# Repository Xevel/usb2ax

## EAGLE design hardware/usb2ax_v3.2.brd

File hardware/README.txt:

usb2ax Eagle files
==================

usb2ax_v3.2 : Second production version, cheaper (uses OPL parts instead of some costly components).

usb2ax_v3.1 : First production version. Added protection against short-circuit between +12V and DATA, and better hackability (expension pads).

usb2ax_mini : A smaller version of the v3.0 with a PCB USB connector and audacious placement of the Dynamixel connector.

usb2ax_v3.0 : MCU in QFN package, real USB connector

usb2ax_v2 (removed) : aborted version similar to v1.

usb2ax_v1 : Initial realease. MCu in TQFP package, PCB USB connector, protections lacking.

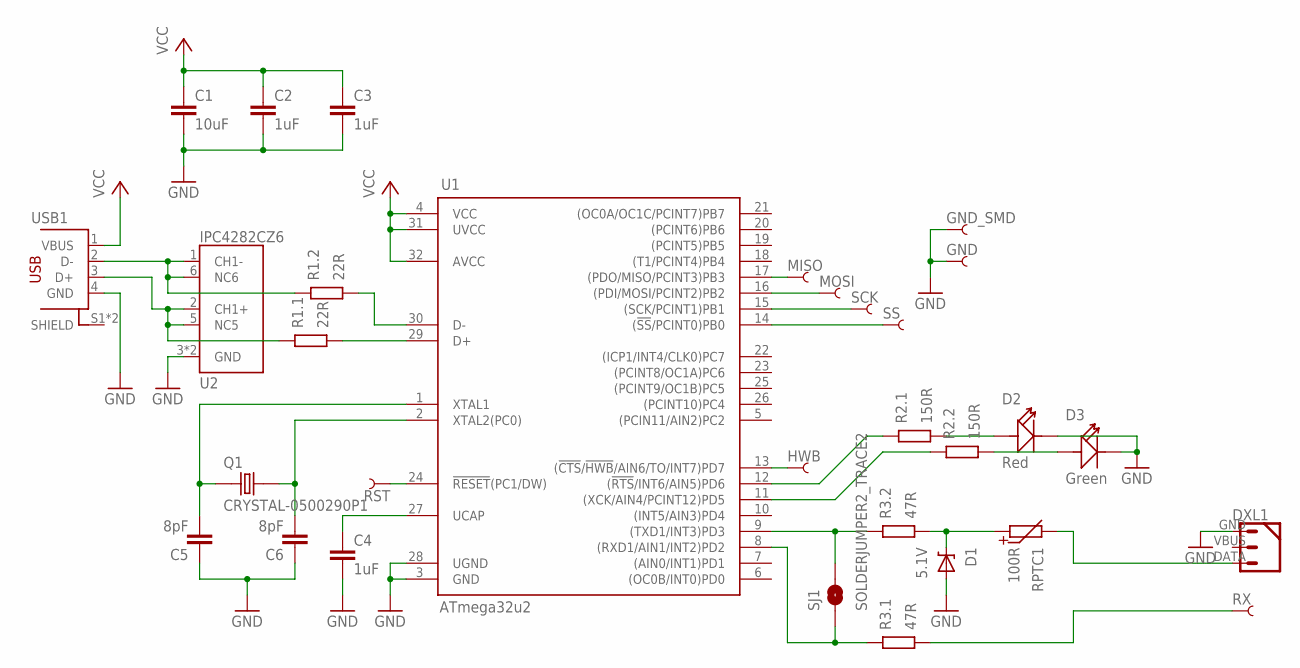
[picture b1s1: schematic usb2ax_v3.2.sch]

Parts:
C1: 10uF; 0805_L
C2, C3, C4: 1uF; 0402_N
C5, C6: 8pF; 0402_N
D1: 5.1V; SOD-923_N
D2: Red; LED0603
D3: Green; LED0603
DXL1: DYNAMIXEL_3POS; DYMANIXEL_3POS_RIGHT
GND: PIN_SMD_2X2.5
GND_SMD: PIN_SMD_2X2.5
HWB: PIN_SMD_2X2.5
MISO: PIN_SMD_2X2.5
MOSI: PIN_SMD_2X2.5
Q1: CRYSTAL-0500290P1; 2P-SMD-5.0X3.2
R1: 22R; ARRAY_0402_65P_2_N
R2: 150R; ARRAY_0402_65P_2_N
R3: 47R; ARRAY_0402_65P_2_N
RPTC1: 100R; 0603_N
RST: PIN_SMD_2X2.5
RX: PIN_THT_0.8; PIN_0.8
SCK: PIN_SMD_2X2.5
SJ1: SOLDERJUMPER2_TRACE2; SJ_2S-TRACE2
SS: PIN_SMD_2X2.5
U1: ATmega32u2; QFN-32_50P_L_MOD
U2: IPC4282CZ6; XSON6_N
USB1: USB-STANDARD-PLUG_A_THT; USB-A-THT

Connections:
GND: C1.2, C2.2, C3.2, C4.2, C5.1, C6.1, D1.A, D2.-, D3.-, DXL1.GND (1), GND.PIN, GND_SMD.PIN, U1.3 (GND), U1.28 (UGND), U2.3 (GND), U2.4 (GND), USB1.4 (GND)
HWB: HWB.PIN, U1.13 ((!CTS!/!HWB!/AIN6/TO/INT7)PD7)
unnamed: R3.4 (2), SJ1.2, U1.9 ((TXD1/INT3)PD3)
unnamed: R3.3 (2), SJ1.1, U1.8 ((RXD1/AIN1/INT2)PD2)
unnamed: C4.1, U1.27 (UCAP)
unnamed: D1.C, R3.1, RPTC1.1
unnamed: R2.4 (2), U1.11 ((XCK/AIN4/PCINT12)PD5)
unnamed: DXL1.DATA (3), RPTC1.2
unnamed: C6.2, Q1.2, U1.2 (XTAL2(PC0))
unnamed: C5.2, Q1.1, U1.1 (XTAL1)
unnamed: R1.1, U1.30 (D-)
unnamed: R1.2 (1), U1.29 (D+)
unnamed: R1.4 (2), U2.1 (CH1-), U2.6 (NC6), USB1.2 (D-)
unnamed: R1.3 (2), U2.2 (CH1+), U2.5 (NC5), USB1.3 (D+)
unnamed: D2.+, R2.2 (1)
unnamed: D3.+, R2.1
unnamed: R2.3 (2), U1.12 ((!RTS!/INT6/AIN5)PD6)
unnamed: R3.2 (1), RX.PIN
unnamed: MISO.PIN, U1.17 ((PDO/MISO/PCINT3)PB3)
unnamed: MOSI.PIN, U1.16 ((PDI/MOSI/PCINT2)PB2)
unnamed: SCK.PIN, U1.15 ((SCK/PCINT1)PB1)
unnamed: SS.PIN, U1.14 ((!SS!/PCINT0)PB0)
RST: RST.PIN, U1.24 (!RESET!(PC1/DW))
VCC: C1.1, C2.1, C3.1, U1.4 (VCC), U1.31 (UVCC), U1.32 (AVCC), USB1.1 (VBUS)

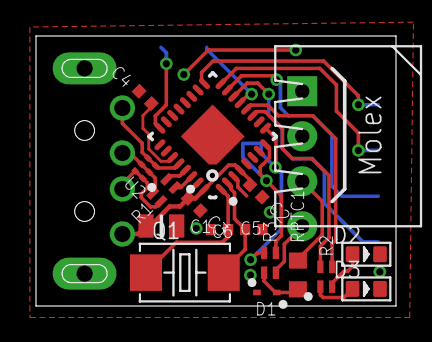
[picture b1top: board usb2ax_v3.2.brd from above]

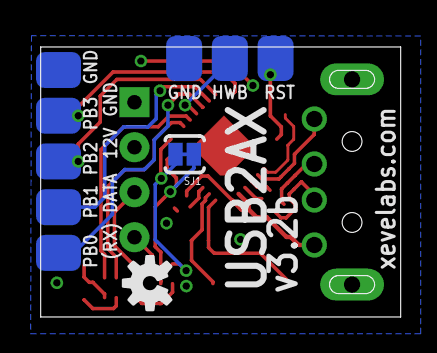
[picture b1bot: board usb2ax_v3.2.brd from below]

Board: 2 copper layers, 20.0 x 15.0 mm, 29 parts (10 on the bottom side), 24 nets.

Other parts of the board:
U$1: OSHW-LOGO-S

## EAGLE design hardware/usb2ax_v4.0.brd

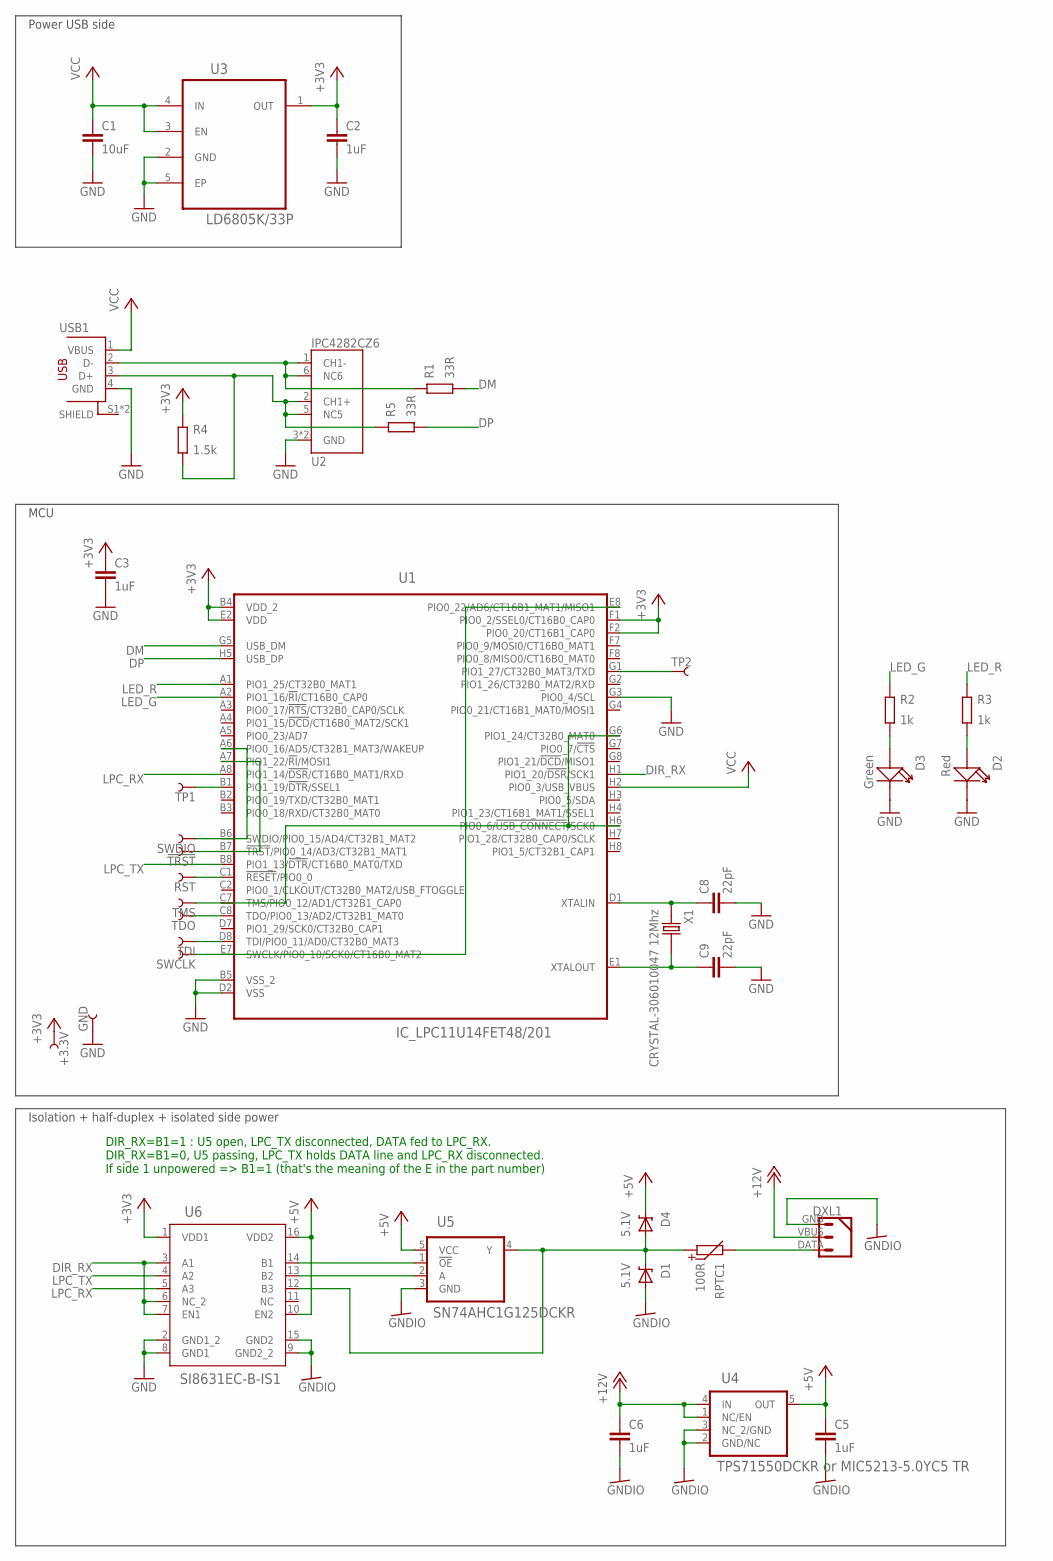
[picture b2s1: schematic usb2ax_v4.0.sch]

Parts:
!TRST: PIN_SMD_1X1
+3.3V: PIN_SMD_1X1
C1: 10uF; 0805_L
C2, C3, C5, C6: 1uF; 0402_N
C8, C9: 22pF; 0402_N
D1, D4: 5.1V; SOD-923_N
D2: Red; LED0603
D3: Green; LED0603
DXL1: DYNAMIXEL_3POS-R; DYNAMIXEL_3POS_RIGHT
GND: PIN_SMD_1X1
R1, R5: 33R; 0201_N
R2, R3: 1k; 0201_N
R4: 1.5k; 0201_N
RPTC1: 100R; 0603_N
RST: PIN_SMD_1X1
SWCLK: PIN_SMD_1X1
SWDIO: PIN_SMD_1X1
TDI: PIN_SMD_1X1
TDO: PIN_SMD_1X1
TMS: PIN_SMD_1X1
TP1, TP2: PIN_SMD_1X1
U1: IC_LPC11U14FET48/201; BGA48C50P8X8_460X460X110
U2: IPC4282CZ6; XSON6_N
U3: LD6805K/33P; NXP_LD6805
U4: TPS71550DCKR or MIC5213-5.0YC5 TR; SOT65P210X110-5N
U5: SN74AHC1G125DCKR; SOT65P210X110-5N
U6: SI8631EC-B-IS1; SOIC-16
USB1: USB-STANDARD-PLUG_A_THT; USB-A-THT
X1: CRYSTAL-306010047 12Mhz; 2P-SMD-5.0X3.2

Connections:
!TRST: !TRST.P$1, U1.A7 (PIO1_22/!RI!/MOSI1), U1.B7 (!TRST!/PIO0_14/AD3/CT32B1_MAT1)
+3V3: +3.3V.P$1, C2.1, C3.1, R4.2, U1.B4 (VDD_2), U1.E2 (VDD), U1.F1 (PIO0_2/SSEL0/CT16B0_CAP0), U1.F2 (PIO0_20/CT16B1_CAP0), U3.1 (OUT), U6.1 (VDD1)
+5V: C5.1, D4.C, U4.5 (OUT), U5.5 (VCC), U6.10 (EN2), U6.16 (VDD2)
+12V: C6.1, DXL1.VBUS (2), U4.1 (NC/EN), U4.4 (IN)
DIR_RX: U1.H1 (PIO1_20/!DSR!/SCK1), U6.3 (A1), U6.6 (NC_2), U6.7 (EN1)
DM: R1.1, U1.G5 (USB_DM)
DP: R5.1, U1.H5 (USB_DP)
GND: C1.2, C2.2, C3.2, C8.2, C9.2, D2.-, D3.-, GND.P$1, U1.B5 (VSS_2), U1.D2 (VSS), U1.G3 (PIO0_4/SCL), U2.3 (GND), U2.4 (GND), U3.2 (GND), U3.5 (EP), U6.2 (GND1_2), U6.8 (GND1), USB1.4 (GND)
GNDIO: C5.2, C6.2, D1.A, DXL1.GND (1), U4.2 (GND/NC), U4.3 (NC_2/GND), U5.3 (GND), U6.9 (GND2_2), U6.15 (GND2)
LED_G: R2.2, U1.A2 (PIO1_16/!RI!/CT16B0_CAP0)
LED_R: R3.2, U1.A1 (PIO1_25/CT32B0_MAT1)
LPC_RX: U1.A8 (PIO1_14/!DSR!/CT16B0_MAT1/RXD), U6.5 (A3)
LPC_TX: U1.B8 (PIO1_13/!DTR!/CT16B0_MAT0/TXD), U6.4 (A2)
unnamed: TP1.P$1, U1.B1 (PIO1_19/!DTR!/SSEL1)
unnamed: D3.+, R2.1
unnamed: U5.2 (A), U6.13 (B2)
unnamed: D1.C, D4.A, RPTC1.1, U5.4 (Y), U6.12 (B3)
unnamed: TP2.P$1, U1.G1 (PIO1_27/CT32B0_MAT3/TXD)
unnamed: DXL1.DATA (3), RPTC1.2
unnamed: C9.1, U1.E1 (XTALOUT), X1.2
unnamed: C8.1, U1.D1 (XTALIN), X1.1
unnamed: D2.+, R3.1
unnamed: R1.2, U2.1 (CH1-), U2.6 (NC6), USB1.2 (D-)
unnamed: R4.1, R5.2, U2.2 (CH1+), U2.5 (NC5), USB1.3 (D+)
unnamed: U5.1 (!OE), U6.14 (B1)
RST: RST.P$1, U1.C1 (!RESET!/PIO0_0)
SWCLK: SWCLK.P$1, U1.E7 (SWCLK/PIO0_10/SCK0/CT16B0_MAT2), U1.E8 (PIO0_22/AD6/CT16B1_MAT1/MISO1)
SWDIO: SWDIO.P$1, U1.A6 (PIO0_16/AD5/CT32B1_MAT3/WAKEUP), U1.B6 (SWDIO/PIO0_15/AD4/CT32B1_MAT2)
TDI: TDI.P$1, U1.D8 (TDI/PIO0_11/AD0/CT32B0_MAT3)
TDO: TDO.P$1, U1.C8 (TDO/PIO0_13/AD2/CT32B1_MAT0)
TMS: TMS.P$1, U1.C7 (TMS/PIO0_12/AD1/CT32B1_CAP0), U1.G6 (PIO1_24/CT32B0_MAT0), U1.H6 (PIO0_6/!USB_CONNECT!/SCK0)
VCC: C1.1, U1.H2 (PIO0_3/USB_VBUS), U3.3 (EN), U3.4 (IN), USB1.1 (VBUS)

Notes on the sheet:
DIR_RX=B1=1 : U5 open, LPC_TX disconnected, DATA fed to LPC_RX. DIR_RX=B1=0, U5 passing, LPC_TX holds DATA line and LPC_RX disconnected. If side 1 unpowered => B1=1 (that's the meaning of the E in the part number)
Isolation + half-duplex + isolated side power
MCU
Power USB side

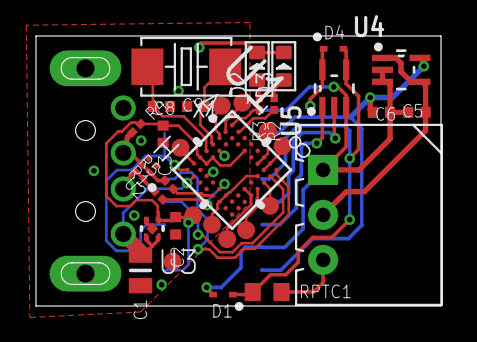
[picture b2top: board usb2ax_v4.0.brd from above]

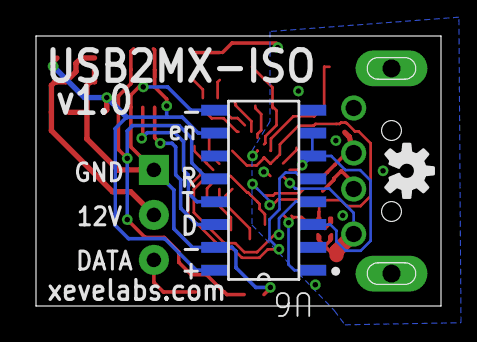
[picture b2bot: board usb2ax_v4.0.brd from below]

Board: 2 copper layers, 22.5 x 15.0 mm, 38 parts (2 on the bottom side), 32 nets.

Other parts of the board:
U$1: OSHW-LOGO-S

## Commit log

2014-02-23 Import of the data from paranoidstudio repo - with slight cleanup of the folder tree.
2014-02-24 Added the Dynamixel_SDK code with sync_read and sync_write.
2014-02-24 small fix in a demo bat file to program the USB2AX with dfu-programmer
2014-02-25 Removed a mod that was for a version interfacing with RS485 servos using a MAX485. It will be reborn in a branch.
2014-02-25 Modif to use PB1 as direction output for a RS485 transciever.
2014-02-25 Cleanup: the timeout for sync_read is already good enough.
2014-03-07 Updated link to the (fixed) code of the reboot/bootload trick
2014-12-29 Added USB2AX v4 first hardware rev. WIP.
2014-12-30 v4 hardware: sch probably done, tentative routing.
2014-12-30 v4 hardware probably done.
2014-12-30 usb2ax_serial: added pull ups on RX
2015-01-17 [firmware] Added Ping command
2015-01-17 [Firmware] fixed crash upon reading from the USB2AX before talking to servos.
2015-01-18 [firmware] fixed perf penalty for packets >8bytes long, added debug functionalities.
2015-01-19 [firmware] added write_data command and dynamic Dynamixel table (the values of which are currently not used by the rest of the program...)
2015-01-20 [firmware] Added eeprom saving and recovery of registers (and return to default with "reset" command). Registers still not in use though.
2015-01-20 [firmware] use registers for timeouts parameters.
2015-01-20 [Test app] Updated for VS2012
2015-02-04 Now there is no retention of the bytes coming from the host: every command is transmitted directly to the bus, even Sync_read. The servos should be able to ignore them anyway, as they are all valid d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
2015-02-04 [firmware] raised the limits of sync_read to nb_servo < 120 && nb_bytes < 122 & nb_servo * nb_bytes < 229.
2015-02-04 [firmware] removed the direct passthrough and use a mode that lets pass full packets without trying to analyze them.
2016-04-06 Upgraded to v3.2b : changed R3 from 150 to 47ohms for stronger line drive
2016-06-26 Updated for programming through hub on Windows 8
2016-09-03 Updated projects to Atmel Studio 7.0
2017-05-07 Code for RS485 can be enabled by a flag in USB2AX.c. Use PB1 for direction select on transceiver.
2017-06-29 [firmware] v05RC0 * Increased ToUSB_Buffer_Data size from 128 to 254. This seems to have resolved the issue where a read on a device with a long table (176 bytes) would cause the board to randomly lo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
    * Anticipated the moment when interruptions are disabled in RingBuffer_Insert and RingBuffer_Remove.
    It is unclear if this is essential: I tested the device without this fix and it also worked with just the increased buffer size. However, this seems like a potential race condition because manipulati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
2017-07-27 Reverted the changes applied to ringbuffer as they were not necessary and thus were over-protective.
2017-07-27 Fix for the spurious error messages returned to the host by the USB2AX when DXL2.0 packets are issued. Thanks to Tho- Updated binary to RC1.
2017-07-27 Added v05 RC1 binary (for real this time)
2017-11-15 Updated the solution of the updater, and fixed a null ref exception
2017-11-15 Changed python script to be linux-ready as that's when it's most useful

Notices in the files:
parts and their libraries:
SparkFun-Aesthetics: Licensing: CC v3.0 Share-Alike You are welcome to use this library for commercial purposes.
